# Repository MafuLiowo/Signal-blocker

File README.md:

# Signal-blocker
Signal-blocker,named as what it is!

PCB Board!

Minimal version are now available!!!

2.5cm  x  3.8cm !!!!!

How to use:
  the BOM excel includes all the things you need.

  The release file is the file you need to hand in to the PCB manufaturer.

  Like JLCPCB,Foxconn,SCC,TTM Technologies.

  It may cost some fee.

Language support:

  简体中文 日本語 English

VCO module can be replaced to anyother VCO module to block any frequence!

recommended:GSM/CDMA TD-LTE MICROWAVE

物如其名

VCO可随意更换其他VCO模组

推荐模组：GSM/CDMA TD-LTE MICROWAVE

物は名の通り

VCOは他のVCOモジュールに自由に交換可能

推奨モジュール：GSM/CDMA TD-LTE MICROWAVE

First version being released!

This is the first project I released in Github

Anyway of usage is allowed,including editing、modifying、fixing

Thank you for your star!

给颗星星谢谢啦！

ありがとうございます

( '﹃'⑉)

X(twitter) @Mafumafuowo

Mail:Mafumafuowo@gmail.com

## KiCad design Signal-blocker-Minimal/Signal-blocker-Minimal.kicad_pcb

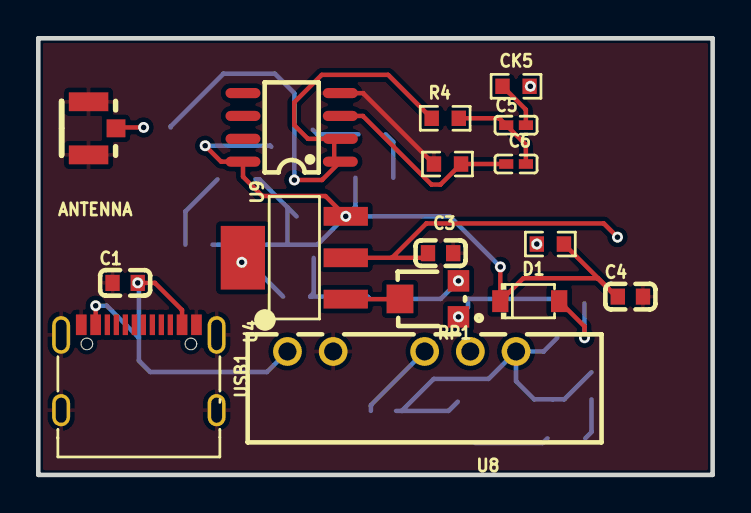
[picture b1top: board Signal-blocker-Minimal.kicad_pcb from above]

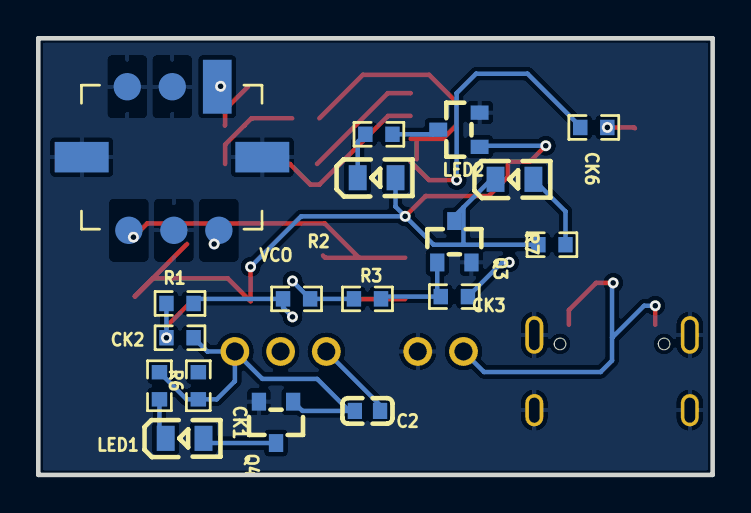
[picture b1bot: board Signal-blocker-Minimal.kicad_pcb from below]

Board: 2 copper layers, 37.5 x 24.3 mm, 34 parts (18 on the bottom side), 16 nets.

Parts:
ANTENNA: wire
C1, C2, C3, C4: C0603
C5, C6: C0402
CK1, CK2, CK3, CK4, CK5, CK6: R0603
D1: SOD-123_L2.7-W1.6-LS3.7-RD
LED1, LED2, LED2#2: LED0805-R-RD
Q3, Q3#2, Q4: S8050_SOT-23
R1, R2, R3, R4, R5, R6, R6#2, R7: R0603
RP1: RES-ADJ-SMD_3P-L3.0-W3.8-P1.75-BR
U4: SOT-223_L6.3-W3.5-P2.30-LS7.0-BR
U8: PWRM-TH_A05XXS-1WR3
U9: SOIC-8_L5.0-W4.0-P1.27-LS6.0-BL
USB1: TYPE-C-SMD_HDGC_TYPE-C-ZL-104PWB
VCO: 1234

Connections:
$3N135: ANTENNA.2, CK6.2
$4N521: R2.1, R3.1, RP1.3
$4N526: CK3.2, Q3#2.1, R1.2, R2.2, R3.2, RP1.1
$4N812: CK3.1, U4.4
$5N863: LED2.1, LED2#2.2, R6.2, R7.2
$6N289: C5.2, C6.1, CK5.2, R5.2, U9.3
$6N676: C5.1, C6.2, R4.1
ADJ: RP1.2, U4.1
GND: ANTENNA.1, ANTENNA.3, C1.1, C3.1, C4.2, Q3.2, Q3#2.2, Q4.2, R5.1, U8.2, U9.4, USB1.12, USB1.13, USB1.14, USB1.15, USB1.A1B12, USB1.A12B1, VCO.2, VCO.4, VCO.5, VCO.7, VCO.8
POWER: C1.2, U8.1, USB1.A4B9, USB1.A9B4
RFOUT: CK6.1, R4.2, U9.1, U9.2
SIGNAL: CK5.1, VCO.6
VCC9V+: C2.2, CK1.1, CK1.2, CK2.1, LED1.1, LED1.2, Q4.1, Q4.3, R6#2.1, R6#2.2, U8.6
VCC+: C4.1, CK2.2, CK4.1, CK4.2, D1.1, D1.2, LED2.2, LED2#2.1, Q3.1, Q3.3, Q3#2.3, R1.1, R6.1, R7.1, U4.3, U9.8, VCO.1
VCC-: C2.1, U8.4
VT: C3.2, U4.2, VCO.3

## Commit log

2025-02-25 First version being released!
    This is the first project I released in Github
    Anyway of usage is allowed,including editing、modifying、fixing
    Thank you for your star!
    给颗星星谢谢啦！
    ありがとうございます
    ( '﹃'⑉)
2025-02-25 version 2.0.0!
    QWQ
2025-02-25 version 2.0!
2025-02-25 Minimal version released now!!!
    Minimal version!
    ayaya ayaya
2025-02-26 Version 2.1 Update！
    Fix some circuit!
    More stabler!
    Replace all the restrictor and capacitor into 0603 packaging!
    create BOM excel,Bill of Material.
